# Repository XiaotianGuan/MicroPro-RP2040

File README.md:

**This repository contains the KiCad project, gerber, BOM and other associated files for MicroPro RP2040, a custom RP2040 based dev board compatible with Sparkfun ProMicro RP2040.**

![[Cover]](.pic/cover-1200px.jpg)

The RP2040 is a great microcontroller, plenty powerful, well documented, and cheap. However, its on board ADC kinda sucked. I have another project which incorporates a Sparkfun ProMicro RP2040 board that uses the ADC, and I wish I can get more out of it. 

I really liked the ProMicro form factor. It's relatively small, has plenty of flash and enough GPIO. I also thought it might provide an upgrade path, which turned out to be correct(though that's long before RP2350 was announced). So I decided to design a custom board with a better stand-alone ADC that's drop-in compatible. Meaning the pinout has to stay the same, and the input to the ADC has to be muxed.

The analog pins of the RP2040 (GP26-GP29) are directly wired to the board's pads. While those four pads are also connected to *tmux1204*, a 4:1 mux, whose drain is connected to the *ads7042*, a 1-MSPS, 12-bit, single channel ADC.

![[mux-adc]](.pic/mux-adc.png)

By default, this board should behave no differently than the original. To use the stand-alone ADC, you need to first configure the multiplexer to connect the right pin to the ADC and set the corresponding RP2040 pin to input. This provides better ADC performance, and in theory can achieve 1M sampling rate, double what the on board ADC can do. (Not tested yet.) Though the input filter may need to be redesigned for such high sampling rate.

**Differences**

Though this board is designed to be compatible with Sparkfun ProMicro RP2040, there are a number of differences. First, most significantly, this is a double sided board. Therefore by default it does not have castellated pads, thought a castellated footprint is provided. Second, the push buttons are not the same part used on the Sparkfun board. They're smaller and not as tall, but are at the same position. Third, the pull-up resistance for the qwiic connector is 10k instead of 2.2k, which may limit the maximum I2C clockrate.

![[front]](.pic/front-1200px.jpg)
![[back]](.pic/back-1200px.jpg)

Finally, regarding fabrication. Unlike the Sparkfun board, which uses thin traces and tiny vias. This board is designed for JLCPCB's cheapest 4 layer process. All vias are 0.5mm with 0.3mm drill. USB differential pair is designed for *JLC04081H-3313*, JLC's free tier of impedance controlled boards. Though at 12Mbps, it likely would not have mattered anyway.

By default, this board does not have castellated pads. If your application requires it, replace the footprint for J3 with *12x2 castellated* in the project footprint library. No other modification necessary. Note this will likely incur additional cost for fabrication.

---

# License

The work is released under CC BY-SA 4.0 license.

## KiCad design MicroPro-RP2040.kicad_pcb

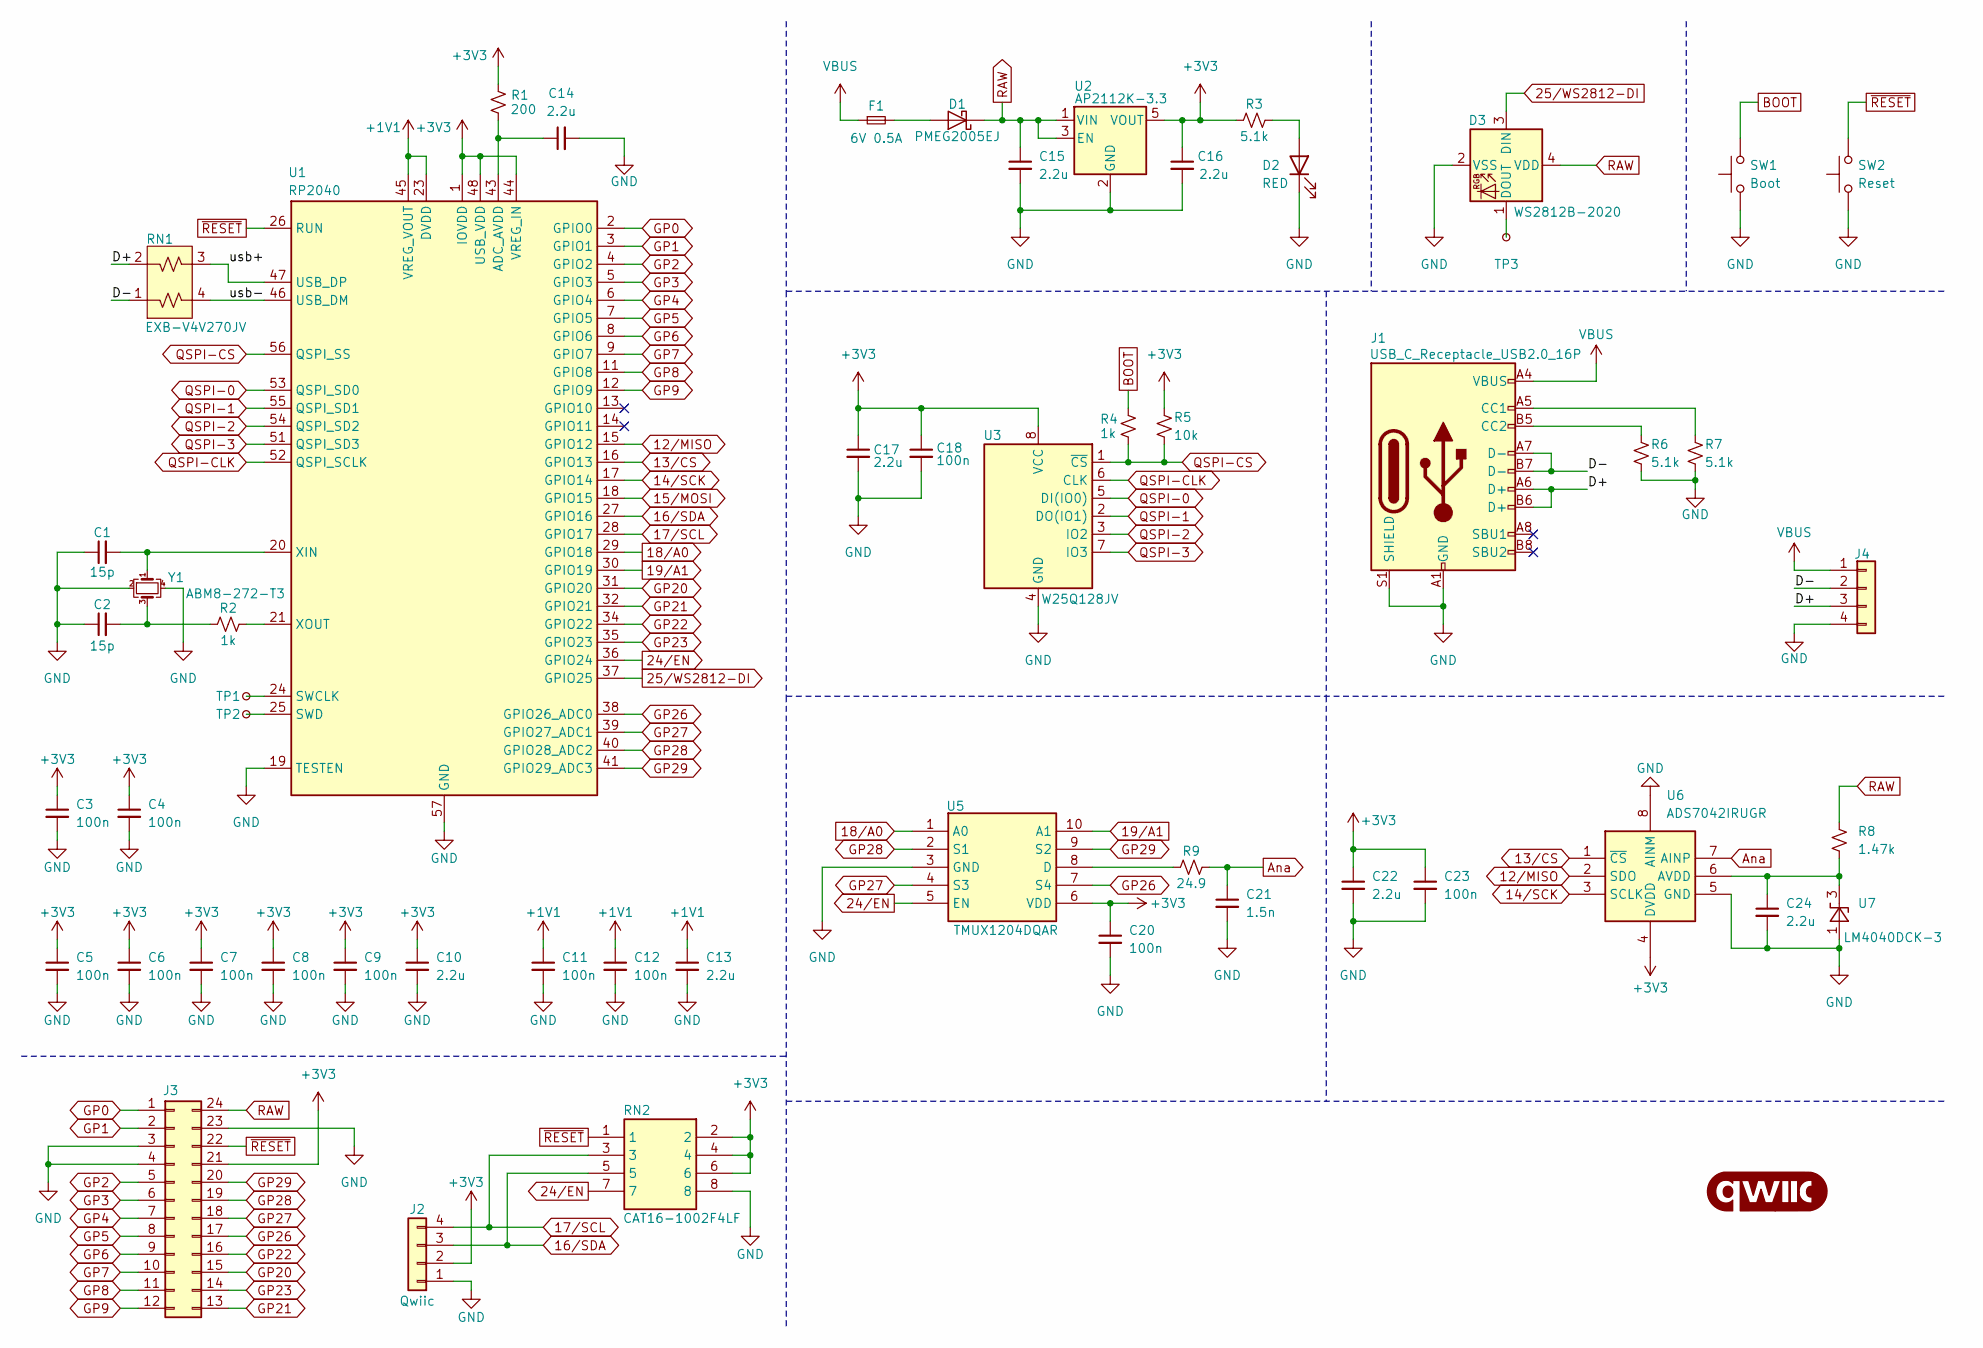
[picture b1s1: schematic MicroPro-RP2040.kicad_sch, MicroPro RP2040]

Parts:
C1, C2: 15p; C_0402_1005Metric
C3, C4, C5, C6, C7, C8, C9, C11, C12, C18, C20, C23: 100n; C_0402_1005Metric
C10, C13, C14, C15, C16, C17, C22, C24: 2.2u; C_0402_1005Metric
C21: 1.5n; C_0402_1005Metric
D1: PMEG2005EJ; D_SOD-323F; Manufacturer_Part_Number PMEG2005EJ-QX
D2: RED; LED_0603_1608Metric
D3: WS2812B-2020; LED_WS2812B-2020_PLCC4_2.0x2.0mm
F1: 6V 0.5A; Fuse_0603_1608Metric; Manufacturer_Part_Number SMD0603B050TF
G1: qwiic_Logo
J1: USB_C_Receptacle_USB2.0_16P; USB_C_Receptacle_GCT_USB4105-xx-A_16P_TopMnt_Horizontal
J2: Qwiic; JST_SH_SM04B-SRSS-TB_1x04-1MP_P1.00mm_Horizontal; Manufacturer_Part_Number SM04B-SRSS-TB(LF)(SN)(P)
J3: Conn_02x12_Counter_Clockwise; 12x2 through hole
J4: Conn_01x04; USB pad
R1: 200; R_0603_1608Metric
R2, R4: 1k; R_0603_1608Metric
R3, R6, R7: 5.1k; R_0603_1608Metric
R5: 10k; R_0603_1608Metric
R8: 1.47k; R_0603_1608Metric
R9: 24.9; R_0603_1608Metric
RN1: EXB-V4V270JV; EXBV4V; Manufacturer_Part_Number EXB-V4V270JV
RN2: CAT16-1002F4LF; CAT16104J4LF; Mouser Part Number 652-CAT16-1003F4LF
SW1: Boot; SW_SPST_B3U-1000P
SW2: Reset; SW_SPST_B3U-1000P
TP1, TP2, TP3: TestPoint_Small; TestPoint_Pad_D1.5mm
U1: RP2040; QFN-56-1EP_7x7mm_P0.4mm_EP3.2x3.2mm
U2: AP2112K-3.3; SOT-23-5; Manufacturer_Part_Number AP2112K-3.3TRG1
U3: W25Q128JV; WSON-8-1EP_6x5mm_P1.27mm_EP3.4x4.3mm; Manufacturer_Part_Number W25Q128JVPIM
U5: TMUX1204DQAR; Mouser Part Number 595-TMUX1204DQAR
U6: ADS7042IRUGR; ADS7056IRUGR; Manufacturer_Part_Number ADS7042IRUGR
U7: LM4040DCK-3; SOT-353_SC-70-5; Manufacturer_Part_Number LM4040A30IDCKR
Y1: ABM8-272-T3; ABM8272T3; Manufacturer_Part_Number ABM8-272-T3

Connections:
12/MISO: U1.15 (GPIO12), U6.2 (SDO)
13/CS: U1.16 (GPIO13), U6.1 (~CS)
14/SCK: U1.17 (GPIO14), U6.3 (SCLK)
15/MOSI: U1.18 (GPIO15)
16/SDA: J2.3, RN2.5, U1.27 (GPIO16)
17/SCL: J2.4, RN2.3, U1.28 (GPIO17)
18/A0: U1.29 (GPIO18), U5.1 (A0)
19/A1: U1.30 (GPIO19), U5.10 (A1)
24/EN: RN2.7, U1.36 (GPIO24), U5.5 (EN)
25/WS2812-DI: D3.3 (DIN), U1.37 (GPIO25)
+1V1: C11.1, C12.1, C13.1, U1.23 (DVDD), U1.45 (VREG_VOUT), U1.50 (DVDD)
+3V3: C3.1, C4.1, C5.1, C6.1, C7.1, C8.1, C9.1, C10.1, C16.1, C17.1, C18.1, C20.1, C22.1, C23.1, J2.2, J3.21, R1.1, R3.1, R5.1, RN2.2, RN2.4, RN2.6, U1.1 (IOVDD), U1.10 (IOVDD), U1.22 (IOVDD), U1.33 (IOVDD), U1.42 (IOVDD), U1.44 (VREG_IN), U1.48 (USB_VDD), U1.49 (IOVDD), U2.5 (VOUT), U3.8 (VCC), U5.6 (VDD), U6.4 (DVDD)
/D+: J1.A6 (D+), J1.B6 (D+), J4.3, RN1.2
/D-: J1.A7 (D-), J1.B7 (D-), J4.2, RN1.1
/usb+: RN1.3, U1.47 (USB_DP)
/usb-: RN1.4, U1.46 (USB_DM)
Ana: C21.1, R9.2, U6.7 (AINP)
BOOT: R4.1, SW1.2
GND: C1.1, C2.1, C3.2, C4.2, C5.2, C6.2, C7.2, C8.2, C9.2, C10.2, C11.2, C12.2, C13.2, C14.2, C15.2, C16.2, C17.2, C18.2, C20.2, C21.2, C22.2, C23.2, C24.2, D2.1 (K), D3.2 (VSS), J1.A1 (GND), J1.A12 (GND), J1.B1 (GND), J1.B12 (GND), J1.S1 (SHIELD), J2.1, J3.3, J3.4, J3.23, J4.4, R6.2, R7.2, RN2.8, SW1.1, SW2.1, U1.19 (TESTEN), U1.57 (GND), U2.2 (GND), U3.4 (GND), U3.9, U5.3 (GND), U6.5 (GND), U6.8 (AINM), U7.1 (A), U7.5 (NC), Y1.2, Y1.4
GP0: J3.1, U1.2 (GPIO0)
GP1: J3.2, U1.3 (GPIO1)
GP2: J3.5, U1.4 (GPIO2)
GP3: J3.6, U1.5 (GPIO3)
GP4: J3.7, U1.6 (GPIO4)
GP5: J3.8, U1.7 (GPIO5)
GP6: J3.9, U1.8 (GPIO6)
GP7: J3.10, U1.9 (GPIO7)
GP8: J3.11, U1.11 (GPIO8)
GP9: J3.12, U1.12 (GPIO9)
GP20: J3.15, U1.31 (GPIO20)
GP21: J3.13, U1.32 (GPIO21)
GP22: J3.16, U1.34 (GPIO22)
GP23: J3.14, U1.35 (GPIO23)
GP26: J3.17, U1.38 (GPIO26_ADC0), U5.7 (S4)
GP27: J3.18, U1.39 (GPIO27_ADC1), U5.4 (S3)
GP28: J3.19, U1.40 (GPIO28_ADC2), U5.2 (S1)
GP29: J3.20, U1.41 (GPIO29_ADC3), U5.9 (S2)
unnamed: C2.2, R2.1, Y1.3
unnamed: D1.2 (A), F1.2
unnamed: D2.2 (A), R3.2
unnamed: D3.1 (DOUT), TP3.1
unnamed: J1.A5 (CC1), R7.1
unnamed: J1.B5 (CC2), R6.1
unnamed: C14.1, R1.2, U1.43 (ADC_AVDD)
unnamed: TP1.1, U1.24 (SWCLK)
unnamed: TP2.1, U1.25 (SWD)
unnamed: C1.2, U1.20 (XIN), Y1.1
unnamed: R2.2, U1.21 (XOUT)
unnamed: R9.1, U5.8 (D)
unnamed: C24.1, R8.2, U6.6 (AVDD), U7.3 (K)
QSPI-0: U1.53 (QSPI_SD0), U3.5 (DI(IO0))
QSPI-1: U1.55 (QSPI_SD1), U3.2 (DO(IO1))
QSPI-2: U1.54 (QSPI_SD2), U3.3 (IO2)
QSPI-3: U1.51 (QSPI_SD3), U3.7 (IO3)
QSPI-CLK: U1.52 (QSPI_SCLK), U3.6 (CLK)
QSPI-CS: R4.2, R5.2, U1.56 (QSPI_SS), U3.1 (~CS)
RAW: C15.1, D1.1 (K), D3.4 (VDD), J3.24, R8.1, U2.1 (VIN), U2.3 (EN)
VBUS: F1.1, J1.A4 (VBUS), J1.A9 (VBUS), J1.B4 (VBUS), J1.B9 (VBUS), J4.1
~RESET: J3.22, RN2.1, SW2.2, U1.26 (RUN)

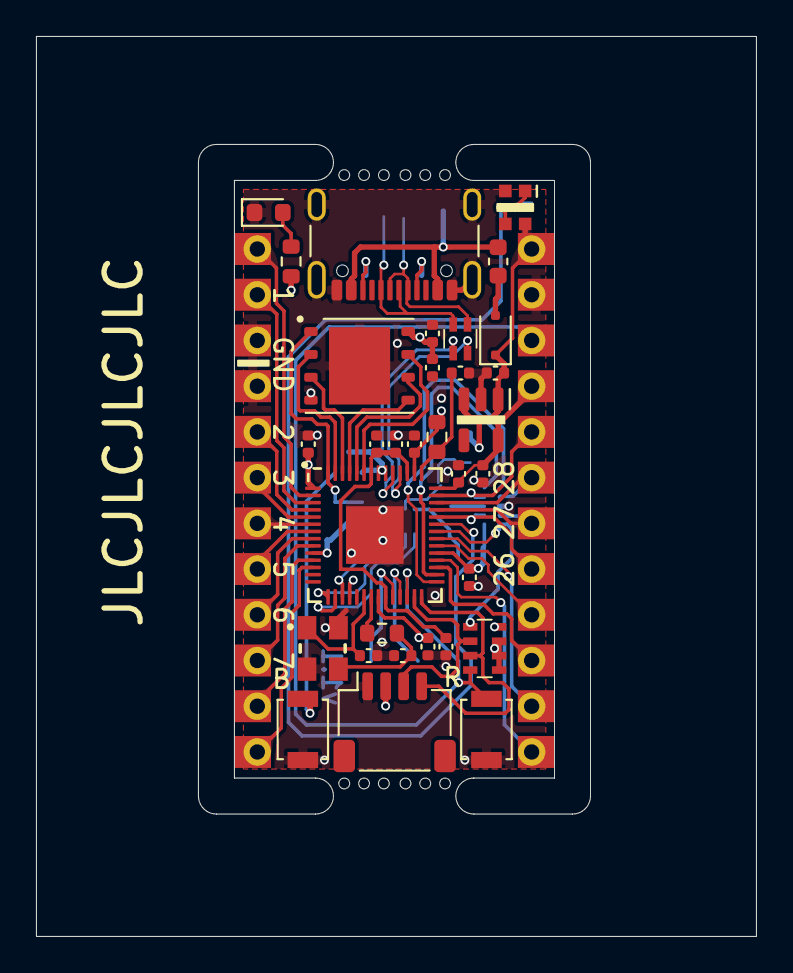
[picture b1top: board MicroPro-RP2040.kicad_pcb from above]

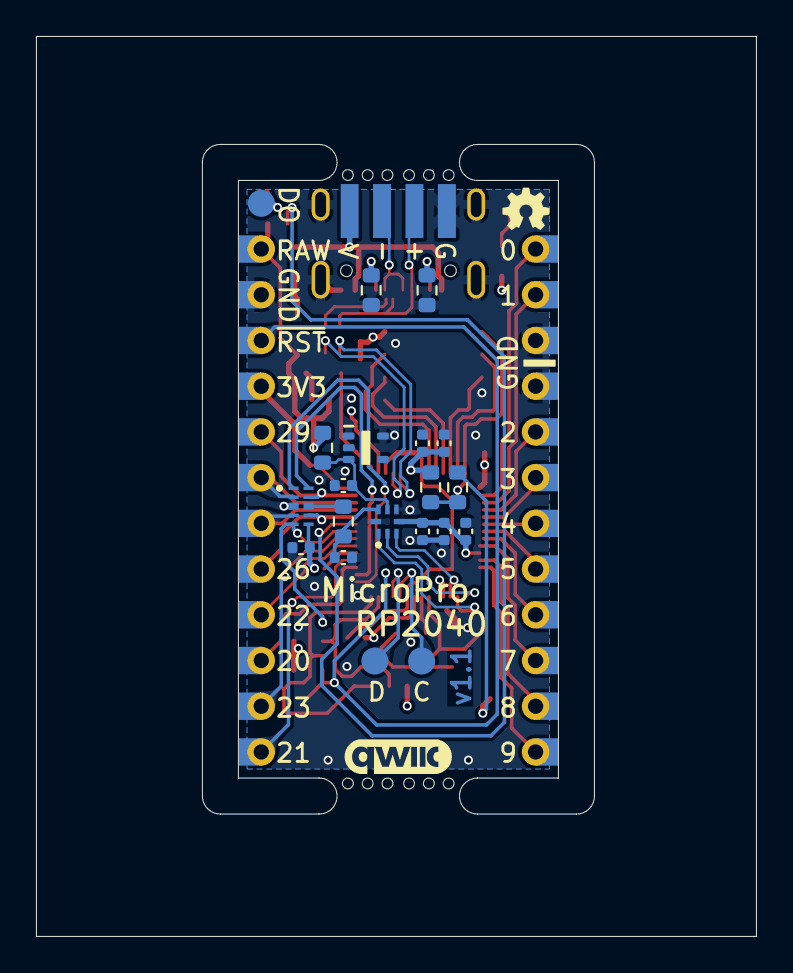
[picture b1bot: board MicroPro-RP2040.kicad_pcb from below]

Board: 4 copper layers, 40.0 x 50.0 mm, 54 parts (21 on the bottom side), 58 nets.

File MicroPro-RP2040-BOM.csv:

"Reference","Value","Footprint","Qty","Manufacturer_Part_Number","Comments"
"C1,C2","15p","Capacitor_SMD:C_0402_1005Metric","2","","C0G dielectric"
"C3,C4,C5,C6,C7,C8,C9,C11,C12,C18,C20,C23","100n","Capacitor_SMD:C_0402_1005Metric","12","",""
"C10,C13,C14,C15,C16,C17,C22,C24","2.2u","Capacitor_SMD:C_0402_1005Metric","8","",""
"C21","1.5n","Capacitor_SMD:C_0402_1005Metric","1","","C0G dielectric"
"D1","PMEG2005EJ","Diode_SMD:D_SOD-323F","1","PMEG2005EJ-QX",""
"D2","RED","LED_SMD:LED_0603_1608Metric","1","",""
"D3","WS2812B-2020","LED_SMD:LED_WS2812B-2020_PLCC4_2.0x2.0mm","1","",""
"F1","6V 0.5A","Fuse:Fuse_0603_1608Metric","1","  SMD0603B050TF",""
"G1","qwiic_Logo","","1","",""
"J1","USB_C_Receptacle_USB2.0_16P","Connector_USB:USB_C_Receptacle_GCT_USB4105-xx-A_16P_TopMnt_Horizontal","1","",""
"J2","Qwiic","Connector_JST:JST_SH_SM04B-SRSS-TB_1x04-1MP_P1.00mm_Horizontal","1","SM04B-SRSS-TB(LF)(SN)(P)",""
"J3","Conn_02x12_Counter_Clockwise","MicroPro:12x2 through hole","1","",""
"J4","Conn_01x04","MicroPro:USB pad","1","",""
"R1","200","Resistor_SMD:R_0603_1608Metric","1","",""
"R2,R4","1k","Resistor_SMD:R_0603_1608Metric","2","",""
"R3,R6,R7","5.1k","Resistor_SMD:R_0603_1608Metric","3","",""
"R5","10k","Resistor_SMD:R_0603_1608Metric","1","",""
"R8","1.47k","Resistor_SMD:R_0603_1608Metric","1","",""
"R9","24.9","Resistor_SMD:R_0603_1608Metric","1","",""
"RN1","EXB-V4V270JV","MicroPro:EXBV4V","1","EXB-V4V270JV",""
"RN2","CAT16-1002F4LF","MicroPro:CAT16104J4LF","1","CAT16-1002F4LF",""
"SW1","Boot","Button_Switch_SMD:SW_SPST_B3U-1000P","1","",""
"SW2","Reset","Button_Switch_SMD:SW_SPST_B3U-1000P","1","",""
"TP1,TP2,TP3","TestPoint_Small","TestPoint:TestPoint_Pad_D1.5mm","3","",""
"U1","RP2040","Package_DFN_QFN:QFN-56-1EP_7x7mm_P0.4mm_EP3.2x3.2mm","1","",""
"U2","AP2112K-3.3","Package_TO_SOT_SMD:SOT-23-5","1","AP2112K-3.3TRG1",""
"U3","W25Q128JV","Package_SON:WSON-8-1EP_6x5mm_P1.27mm_EP3.4x4.3mm","1","W25Q128JVPIM",""
"U5","TMUX1204DQAR","MicroPro:TMUX1204DQAR","1","TMUX1204DQAR",""
"U6","ADS7042IRUGR","MicroPro:ADS7056IRUGR","1","ADS7042IRUGR",""
"U7","LM4040DCK-3","Package_TO_SOT_SMD:SOT-353_SC-70-5","1","LM4040A30IDCKR",""
"Y1","ABM8-272-T3","MicroPro:ABM8272T3","1","ABM8-272-T3",""

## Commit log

2024-10-02 v0.1 initial commit
2024-10-02 removed no longer used sheet
2024-10-03 completed schematics, generated BOM
2024-10-03 fixed typo in schematics
2024-10-04 v1.0 board
2024-10-04 cleaned up schematics
2024-10-04 optimized via position
2024-10-05 fixed miswiring in schematics, v1.1 board
2024-10-22 generated gerber, added license, readme
2024-10-22 edited readme
